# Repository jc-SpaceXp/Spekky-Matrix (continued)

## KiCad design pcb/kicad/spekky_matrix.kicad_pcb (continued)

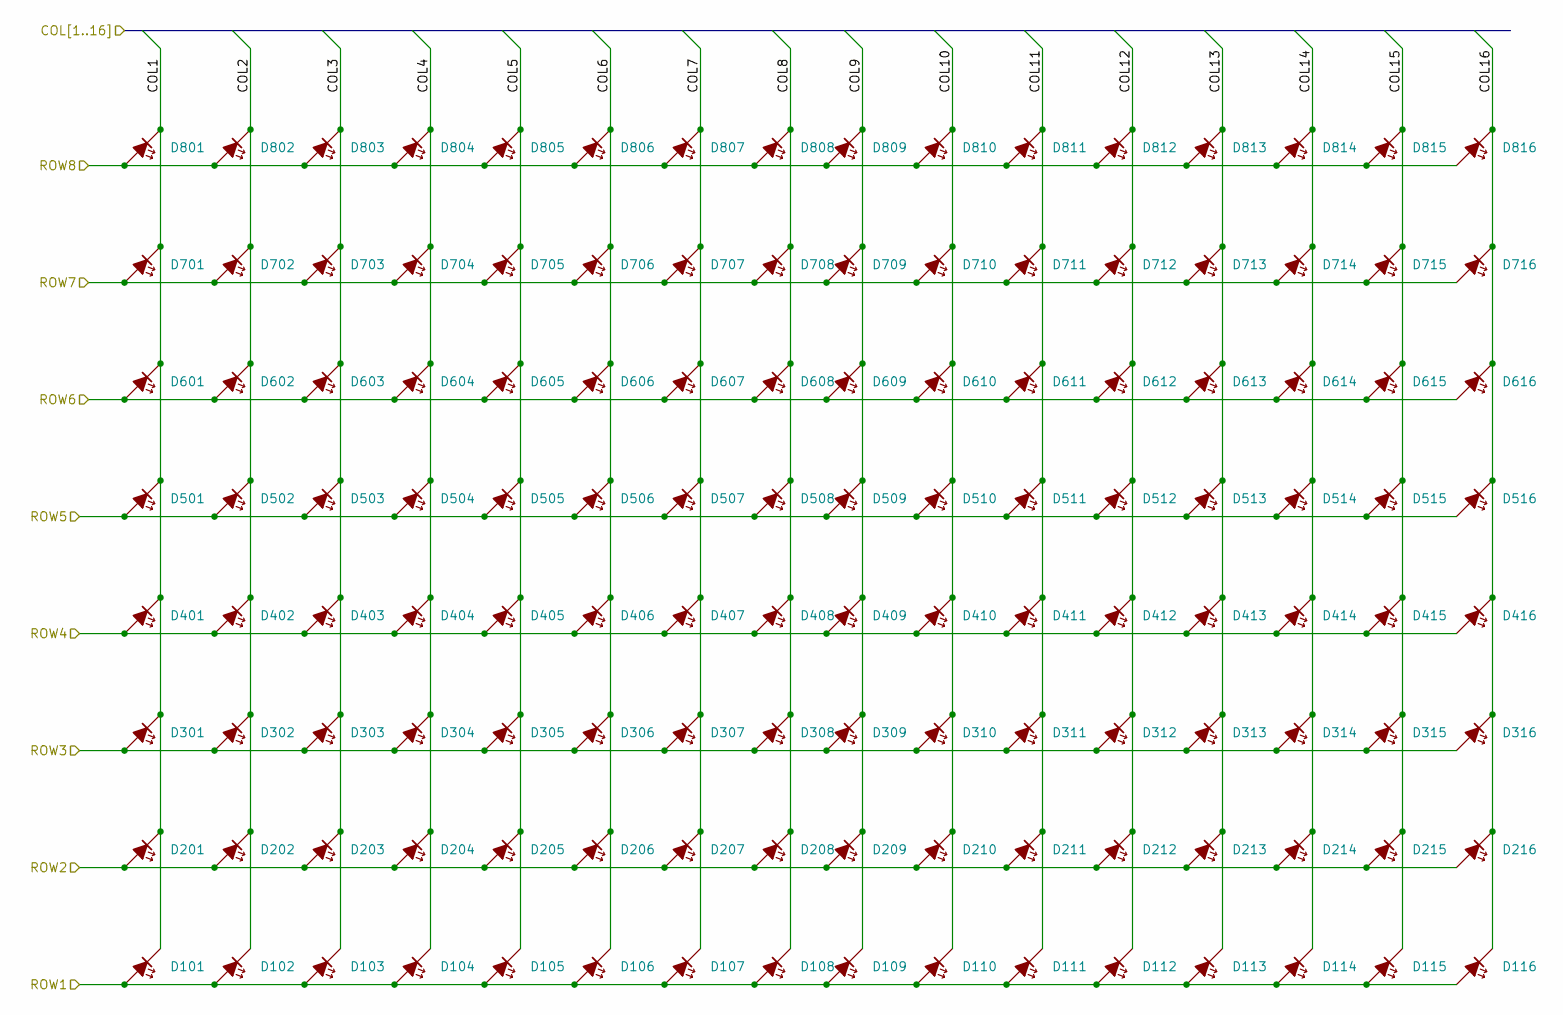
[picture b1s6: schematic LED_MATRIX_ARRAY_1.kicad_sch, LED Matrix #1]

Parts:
D101, D102, D103, D104, D105, D106, D107, D108, D109, D110, D111, D112, D113, D114, D115, D116, D201, D202, D203, D204, D205, D206, D207, D208, D209, D210, D211, D212, D213, D214, D215, D216, D301, D302, D303, D304, D305, D306, D307, D308, D309, D310, D311, D312, D313, D314, D315, D316, D401, D402, D403, D404, D405, D406, D407, D408, D409, D410, D411, D412, D413, D414, D415, D416, D501, D502, D503, D504, D505, D506, D507, D508, D509, D510, D511, D512, D513, D514, D515, D516, D601, D602, D603, D604, D605, D606, D607, D608, D609, D610, D611, D612, D613, D614, D615, D616, D701, D702, D703, D704, D705, D706, D707, D708, D709, D710, D711, D712, D713, D714, D715, D716, D801, D802, D803, D804, D805, D806, D807, D808, D809, D810, D811, D812, D813, D814, D815, D816: LED Matrix (RED); LED_0603_1608Metric_Pad1.05x0.95mm_HandSolder; MPN LTST-C190KRKT

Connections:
/LED DRIVING/COL1: D101.1 (K), D201.1 (K), D301.1 (K), D401.1 (K), D501.1 (K), D601.1 (K), D701.1 (K), D801.1 (K); also elsewhere on the board
/LED DRIVING/COL2: D102.1 (K), D202.1 (K), D302.1 (K), D402.1 (K), D502.1 (K), D602.1 (K), D702.1 (K), D802.1 (K); also elsewhere on the board
/LED DRIVING/COL3: D103.1 (K), D203.1 (K), D303.1 (K), D403.1 (K), D503.1 (K), D603.1 (K), D703.1 (K), D803.1 (K); also elsewhere on the board
/LED DRIVING/COL4: D104.1 (K), D204.1 (K), D304.1 (K), D404.1 (K), D504.1 (K), D604.1 (K), D704.1 (K), D804.1 (K); also elsewhere on the board
/LED DRIVING/COL5: D105.1 (K), D205.1 (K), D305.1 (K), D405.1 (K), D505.1 (K), D605.1 (K), D705.1 (K), D805.1 (K); also elsewhere on the board
/LED DRIVING/COL6: D106.1 (K), D206.1 (K), D306.1 (K), D406.1 (K), D506.1 (K), D606.1 (K), D706.1 (K), D806.1 (K); also elsewhere on the board
/LED DRIVING/COL7: D107.1 (K), D207.1 (K), D307.1 (K), D407.1 (K), D507.1 (K), D607.1 (K), D707.1 (K), D807.1 (K); also elsewhere on the board
/LED DRIVING/COL8: D108.1 (K), D208.1 (K), D308.1 (K), D408.1 (K), D508.1 (K), D608.1 (K), D708.1 (K), D808.1 (K); also elsewhere on the board
/LED DRIVING/COL9: D109.1 (K), D209.1 (K), D309.1 (K), D409.1 (K), D509.1 (K), D609.1 (K), D709.1 (K), D809.1 (K); also elsewhere on the board
/LED DRIVING/COL10: D110.1 (K), D210.1 (K), D310.1 (K), D410.1 (K), D510.1 (K), D610.1 (K), D710.1 (K), D810.1 (K); also elsewhere on the board
/LED DRIVING/COL11: D111.1 (K), D211.1 (K), D311.1 (K), D411.1 (K), D511.1 (K), D611.1 (K), D711.1 (K), D811.1 (K); also elsewhere on the board
/LED DRIVING/COL12: D112.1 (K), D212.1 (K), D312.1 (K), D412.1 (K), D512.1 (K), D612.1 (K), D712.1 (K), D812.1 (K); also elsewhere on the board
/LED DRIVING/COL13: D113.1 (K), D213.1 (K), D313.1 (K), D413.1 (K), D513.1 (K), D613.1 (K), D713.1 (K), D813.1 (K); also elsewhere on the board
/LED DRIVING/COL14: D114.1 (K), D214.1 (K), D314.1 (K), D414.1 (K), D514.1 (K), D614.1 (K), D714.1 (K), D814.1 (K); also elsewhere on the board
/LED DRIVING/COL15: D115.1 (K), D215.1 (K), D315.1 (K), D415.1 (K), D515.1 (K), D615.1 (K), D715.1 (K), D815.1 (K); also elsewhere on the board
/LED DRIVING/COL16: D116.1 (K), D216.1 (K), D316.1 (K), D416.1 (K), D516.1 (K), D616.1 (K), D716.1 (K), D816.1 (K); also elsewhere on the board
/LED DRIVING/ROW1: D101.2 (A), D102.2 (A), D103.2 (A), D104.2 (A), D105.2 (A), D106.2 (A), D107.2 (A), D108.2 (A), D109.2 (A), D110.2 (A), D111.2 (A), D112.2 (A), D113.2 (A), D114.2 (A), D115.2 (A), D116.2 (A); also elsewhere on the board
/LED DRIVING/ROW2: D201.2 (A), D202.2 (A), D203.2 (A), D204.2 (A), D205.2 (A), D206.2 (A), D207.2 (A), D208.2 (A), D209.2 (A), D210.2 (A), D211.2 (A), D212.2 (A), D213.2 (A), D214.2 (A), D215.2 (A), D216.2 (A); also elsewhere on the board
/LED DRIVING/ROW3: D301.2 (A), D302.2 (A), D303.2 (A), D304.2 (A), D305.2 (A), D306.2 (A), D307.2 (A), D308.2 (A), D309.2 (A), D310.2 (A), D311.2 (A), D312.2 (A), D313.2 (A), D314.2 (A), D315.2 (A), D316.2 (A); also elsewhere on the board
/LED DRIVING/ROW4: D401.2 (A), D402.2 (A), D403.2 (A), D404.2 (A), D405.2 (A), D406.2 (A), D407.2 (A), D408.2 (A), D409.2 (A), D410.2 (A), D411.2 (A), D412.2 (A), D413.2 (A), D414.2 (A), D415.2 (A), D416.2 (A); also elsewhere on the board
/LED DRIVING/ROW5: D501.2 (A), D502.2 (A), D503.2 (A), D504.2 (A), D505.2 (A), D506.2 (A), D507.2 (A), D508.2 (A), D509.2 (A), D510.2 (A), D511.2 (A), D512.2 (A), D513.2 (A), D514.2 (A), D515.2 (A), D516.2 (A); also elsewhere on the board
/LED DRIVING/ROW6: D601.2 (A), D602.2 (A), D603.2 (A), D604.2 (A), D605.2 (A), D606.2 (A), D607.2 (A), D608.2 (A), D609.2 (A), D610.2 (A), D611.2 (A), D612.2 (A), D613.2 (A), D614.2 (A), D615.2 (A), D616.2 (A); also elsewhere on the board
/LED DRIVING/ROW7: D701.2 (A), D702.2 (A), D703.2 (A), D704.2 (A), D705.2 (A), D706.2 (A), D707.2 (A), D708.2 (A), D709.2 (A), D710.2 (A), D711.2 (A), D712.2 (A), D713.2 (A), D714.2 (A), D715.2 (A), D716.2 (A); also elsewhere on the board
/LED DRIVING/ROW8: D801.2 (A), D802.2 (A), D803.2 (A), D804.2 (A), D805.2 (A), D806.2 (A), D807.2 (A), D808.2 (A), D809.2 (A), D810.2 (A), D811.2 (A), D812.2 (A), D813.2 (A), D814.2 (A), D815.2 (A), D816.2 (A); also elsewhere on the board

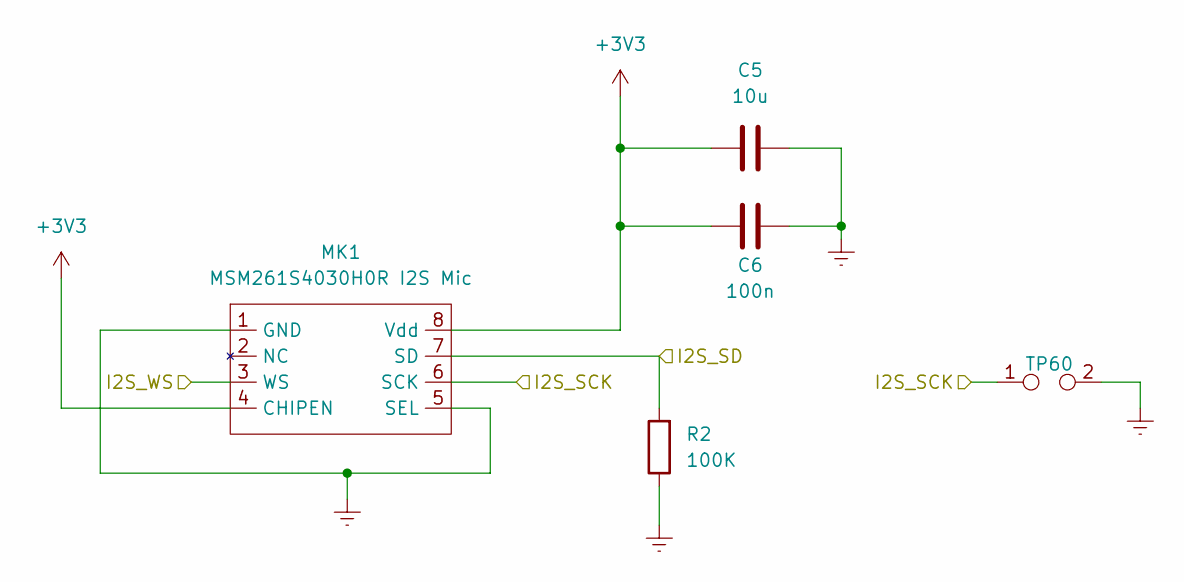
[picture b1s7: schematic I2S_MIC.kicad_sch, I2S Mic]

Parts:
C5: 10u; C_0603_1608Metric; MPN C1608X5R1A106K080AC
C6: 100n; C_0603_1608Metric; MPN C0603C104J3RACTU
MK1: MSM261S4030H0R I2S Mic; LGA-8_2x4_3.0x4.0mm_P1.0mm_Hand_Solder; MPN MSM261S4030H0R
R2: 100K; R_0603_1608Metric; MPN RP73PF1J100KBTDF
TP60: TestPoint_2Pole; D_MicroMELF

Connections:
+3V3: C5.2, C6.2, MK1.4 (CHIPEN), MK1.8 (Vdd); also elsewhere on the board
/I2S MIC/I2S_SCK: MK1.6 (SCK), TP60.1; also elsewhere on the board
/I2S MIC/I2S_SD: MK1.7 (SD), R2.2; also elsewhere on the board
/I2S MIC/I2S_WS: MK1.3 (WS); also elsewhere on the board
GND: C5.1, C6.1, MK1.1 (GND), MK1.5 (SEL), R2.1, TP60.2; also elsewhere on the board

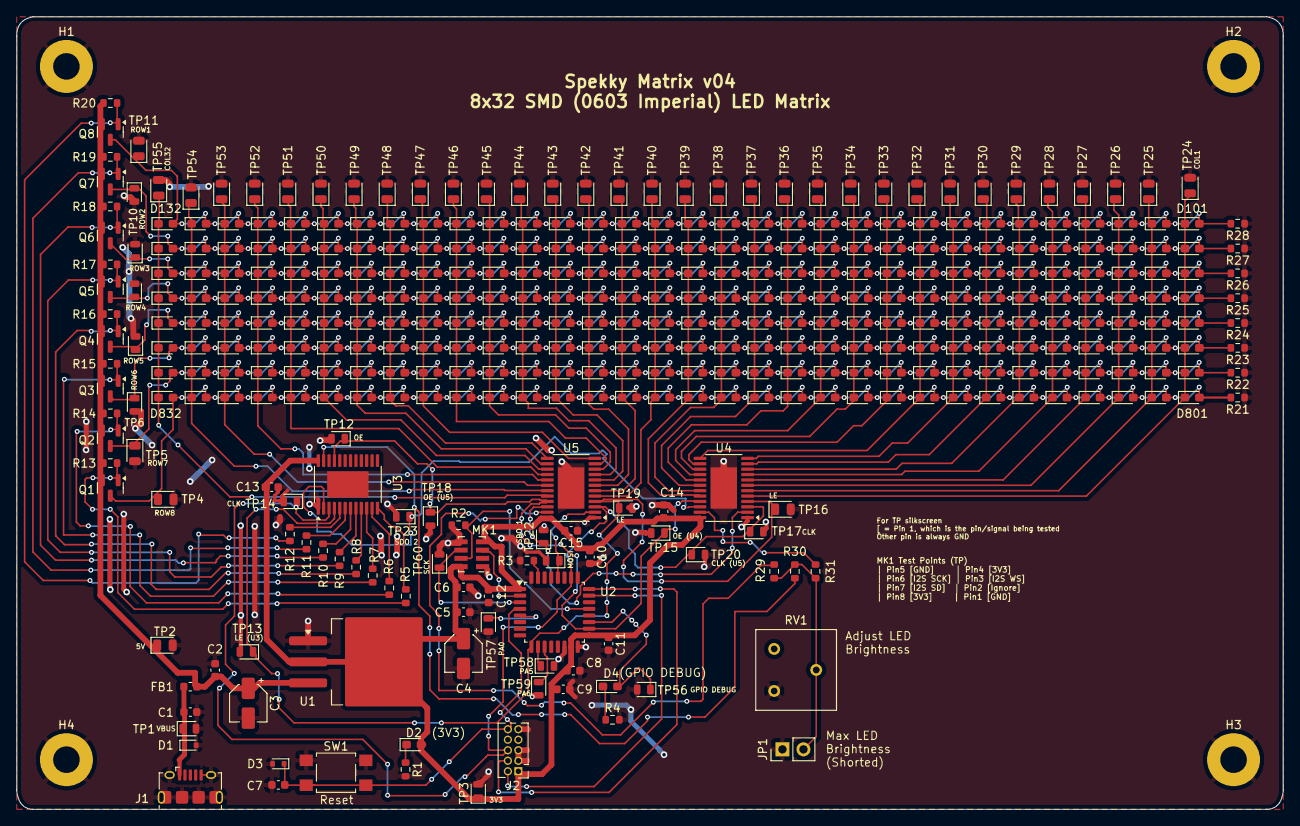
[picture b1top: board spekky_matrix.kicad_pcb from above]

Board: 2 copper layers, 153.0 x 95.8 mm, 390 parts (0 on the bottom side), 83 nets.

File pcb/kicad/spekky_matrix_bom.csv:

"Reference","Qty","MPN","Value","Footprint","DNP"
"C1","1","GCM188R71H103KA37J","10n","Capacitor_SMD:C_0603_1608Metric",""
"C2,C6-C8,C11-C15","9","C0603C104J3RACTU","100n","Capacitor_SMD:C_0603_1608Metric",""
"C3,C4","2","EDH106M016A9BAA","10u","Capacitor_SMD:CP_Elec_4x4.5",""
"C5","1","C1608X5R1A106K080AC","10u","Capacitor_SMD:C_0603_1608Metric",""
"C9","1","GCG188L8EE105KA07D","1u","Capacitor_SMD:C_0603_1608Metric",""
"C10","1","GRM188Z71C475KE21D","4u7","Capacitor_SMD:C_0603_1608Metric",""
"D1,D3","2","PESD5V0X1UAB,115","PESD5V0X1UAB","Diode_SMD:D_SOD-523",""
"D2","1","LTST-C190KRKT","3V3 LED (RED)","LED_SMD:LED_0603_1608Metric_Pad1.05x0.95mm_HandSolder",""
"D4","1","LTST-C190KGKT","GPIO Debug LED (GREEN)","LED_SMD:LED_0603_1608Metric_Pad1.05x0.95mm_HandSolder",""
"D101-D132,D201-D232,D301-D332,D401-D432,D501-D532,D601-D632,D701-D732,D801-D832","256","LTST-C190KRKT","LED Matrix (RED)","LED_SMD:LED_0603_1608Metric_Pad1.05x0.95mm_HandSolder",""
"FB1","1","HI2220R301R-10","300R @ 100 MHz","Inductor_SMD:L_0603_1608Metric",""
"J1","1","10118194-0001LF","USB_B_Micro","Connector_USB:USB_Micro-B_Amphenol_10118194-0001LF_Horizontal",""
"J2","1","FTSH-105-01-L-D-K","Conn_ARM_JTAG_SWD_10","Connector_PinHeader_1.27mm:PinHeader_2x05_P1.27mm_Vertical",""
"MK1","1","MSM261S4030H0R","MSM261S4030H0R I2S Mic","spekky_matrix:LGA-8_2x4_3.0x4.0mm_P1.0mm_Hand_Solder",""
"Q1-Q8","8","DMP3125L-7","DMP3125L-7","Package_TO_SOT_SMD:SOT-23",""
"R1,R4,R13-R20,R29-R31","13","RT0603DRE071KL","1K","Resistor_SMD:R_0603_1608Metric",""
"R2","1","RP73PF1J100KBTDF","100K","Resistor_SMD:R_0603_1608Metric",""
"R3","1","RT0603FRE0710KL","10K","Resistor_SMD:R_0603_1608Metric",""
"R5-R12","8","RT0603FRE0710RL","10R","Resistor_SMD:R_0603_1608Metric",""
"R21-R28","8","RT0603FRE075K1L","5K1","Resistor_SMD:R_0603_1608Metric",""
"RV1","1","3386F-1-222LF","2K2","Potentiometer_THT:Potentiometer_Bourns_3386F_Vertical",""
"SW1","1","TL3305AF260QG","SW_Push","Button_Switch_SMD:SW_SPST_TL3305A",""
"U1","1","LMS1585AIS-3.3/NOPB","LMS1585AIS-3.3","Package_TO_SOT_SMD:TO-263-3_TabPin2",""
"U2","1","STM32G431K8T6","STM32G431K8Tx","Package_QFP:LQFP-32_7x7mm_P0.8mm",""
"U3-U5","3","STP16CP05XTTR ","STP16CP05XT","Package_SO:HTSSOP-24-1EP_4.4x7.8mm_P0.65mm_EP3.2x5mm",""

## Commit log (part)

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2024-05-01 BSP submodule update
    - STM32G431KB update
2024-05-03 Update python fft tests
    - Add option for working with integers rather than floats
2024-05-06 Update CMSIS 6 submodule
2024-05-06 Update main to reflect recent dma changes
    - Dac task is now essentially an idle task as the setup is done before
    all the FreeRTOS code
2024-05-07 Added output of ARM DSP
    - Everything is working as expected, correct bin index and magnitude
    peak (seen on gdb)
    - Dumped gdb array output to text with array indexes to make
    distinguishing real and imaginary values easier
    - Input has to be a complex float, such that x[n] = re(z) and x[n+1] =
    im(z)
2024-05-07 Add python test script file outputs to git ignore
2024-05-08 Update ARM CMSIS 6 submodule
2024-05-08 Remove old c header file from python fft script
    - No longer needed, using ARM DSP, this header was for a different
    submodule
2024-05-09 Make makefile prints easier to see
    - Very hard to see my prints/echos when building this project, added
    some #'s to make those statements more visible (especiall when
    scrolling through the output)
2024-05-20 Place FreeRTOS hooks in its own file
    - Any type of RTOS error handling/hook will be placed in this file in
    the future
    - No header as the FreeRTOS and FreeRTOS tasks headers handle declaring
    the prototype function
    - Unit tests and spekky matrix both compile
2024-05-21 Create oneshot fft timer task
    - I had issues with creating both a oneshot timer "task" and an actual
    preemptive task
    - Kept getting HardFault_Handler errors until I moved the array and
    struct as globals which than gave me a ApplicationStackOverflow error
    (tried this on the oneshot timer)
    - Was able to resolve the oneshot timer method by increasing the timer
2024-06-05 Added STM32 I2S setup for SPI2 module
    - Faced some issues here with my device, looking at the NucleoG431KB
    schematic, PF0 and PF1 (WS and CLK) are both unconnected. Solder
    bridges SB8 and SB11 need to be soldered in order to get an output on
    those pins. Verfied that both WS and CLK were working on my logic
    analyser
    - My I2S MEMS microphone also has a SEL pin which selects which channel
2024-06-07 Remove commented out code
2024-06-18 Add PulseView/Sigrok logic analyser traces
    - With the previous commit I can now graph the logic analyser I2S
    outputs
    - Now have logic analyser traces for:
    1) control (no sound)
    2) 1 kHz sine test tone (played on phone speakers in close proximity
    to Fermion I2S mic)
2024-06-19 Add secondary label for python fft graph
    - Displaying FFT bins as well as frequency too (bins are the top x axis,
    frequency is the bottom, the scalar base on the top left is for the y
    axis e.g. 1e12)
2024-06-19 Refactor fft/ifft graphing code into its own function
2024-06-20 Rename python fft conversion function
    - Function never performed ifft therefore "ifft" bit of string has been
    removed
2024-06-23 Remove TIM2/DAC code from main
    - Timer code is only used for DAC which isn't being used anymore
    - Timer code can also be removed too
2024-06-26 Added new PulseView traces
    - PulseView traces for inverting the I2S idle CLK and a 100K pulldown
    resistor on the I2S SD line
    - Fermion I2S breakout mic also has a 100K pulldown res on SD line too
    as recommended on the I2S mics datasheet
    - Still a couple of non-zero values appear on the R channel but not as
    frequent as before
2024-06-27 Readme: Update submodule list
2024-06-28 Remove awkward 10^x on y axis python FFT graph
    - 10^x label overlaps with the FFT bins top x axis
    - Now 10^x is on each tick on the y axis in scientific notation e.g.
    1.20e11
2024-06-28 Fix readme spacing
2024-09-07 Squashed commit of the following:
    - Opted for squash commit to keep main branch buildable, there was many
    intermediatte commits and hotfixes which shouldn't be on the main
    branch as is
    - Summary of commits:
    1) Processing all incoming I2S mic data into a one channel buffer (w/
    unit tests) (I2S DMA conversion)
2024-09-11 Add kicad pdf schematic of project
    - This is my current schematic which I've implemented by using the
    manhattan prototyping method
    - I consider v01 the single non-cascaded LED matrix version
    - v02 is the 4 cascaded LED matrices
    - Only the pdf for now, I may consider uploading the kicad project later
    as well
2024-09-13 Asan support makefile
2024-09-26 Get timings for led matrix (real speed)
    - Converted LED matrix callback into a task
    - Therefore the only tasks are the IDLE and LED matrix
    - Removed I2S/DMA code as it isn't needed for this timing test
    - Undo the SPI_CLK/8 change to see if we can get an accurate timing of
    the LED matrix task (know it should be ~60us/8 per row, ~60us total)
2024-09-26 Add PulseView traces for spi transfer time
    - Around about 80-90us for the SPI updates to all 4 matrices
2024-09-26 Setup for dma/i2s and fft code only
    - Next commits will be for dma timings and fft task timings
2024-09-26 Get timing for dma to complex data conversion
2024-09-26 Add PulseView traces for fft bin magnitudes
    - As predicted the measured time for FFT bin magnitude calculations was
    150-158us (lo-hi transition time)
    - Can now create an execution timeline figure to add to the project
2024-10-01 New fft led bar sensitivities
    - Skipping the associated unit test until we come up with the final
    values
    - Previous values are way too sensitive, all frequencies have about 4-5
    bars in ambient environments
2024-10-03 Python fft for integer test use square wave
    - Was previously using a sine wave for the configuration of the fft
    - However, seeing as the I2S data is already a 1 kHz wave we are better
    off using a square at max amplitude
    - A square wave at max amplitude allows me to dial in my dB scaling to
    see if it is correct or not
2024-10-04 Capture fft bin magnitude data for max amp square wave
    - Format is 24-bit LSB padding hence 0xFFFFFF00 which is -256 as an int
    positive half cycle
    - Must keep the DMA code as well otherwise a hardfault occurs
2024-10-04 Capture fft bin mags of 24-bit square wave
    - Same test as before except data is LSB padded to 32-bits
2024-10-04 Correct array size in extern declaration
2024-10-05 Add averaging function for 2d arrays
    - Function needed for getting an average that will be fed into the db FS
    conversion function e.g. 6 FFTs into one dB FS calculation
2024-10-05 Additional unit test for averaging function
2024-10-05 Implement fft averaging double buffering via constants
    - Can now just update the fft_constants header file rather than relying
    on hard coded values for FFT averaging double buffering
2024-10-07 Update python fft default options
2024-10-07 Add fixed frequency sine wave output videos
    - 2kHz and 4kHz sine from a youtube video played on my speakers
    - Video are H265 encoded for size
    - Gifs are always large, scaled down to 640x360 to keep the size
    somewhat respectable
2024-10-08 Added sine sweep gif
    - Again used Ffmpeg for this, needed to follow their wiki for "how to
    speed up / slow down a vide", converted to raw h265 and sped up by 2.5
    times speed into a new mp4 file which was then used for a gif
    conversion with the new FPS and gif FPS both matching
    - Found out that changing the FPS of the gif didn't really speed up or
    slow down the video how I wanted
2024-10-31 Update schematic
    - Added no connect pins to unused pins
2024-11-21 Update schematic
    - STM32 part of schematic has been updated, intended to work without the
    Nucelo board now
    - Mostly taken from Nucleo design (VDDA/VDD and GNDA/GND shorts will
    most likely be replaced)
2024-11-26 Update schematic
    - Using USB B micro connector over the bulky USB A
    - Grounded USB shield
    - 5V is now LDO input rather than VBUS to avoid a stubbed VBUS
    transmission line on the PCB
2025-01-25 Led matrix bar function partially supports 16x16 led matricies
    - Required for different LED matrix IC drivers, some expect 16-bit SPI
    transfers, others 8 bit
    - Currently only supporting 8 bits
    - Now supporting 16-bits for RightToLeft and LeftToRight led enum
    directions which supports 16-pixel width (currently hard coded for 8
    rows but could be expanded to 16 rows without any issues)
2025-04-14 Make led cascade function a max7219 specific one
    - Renamed and changed args to be more in line with other recent changes
2025-04-24 Add a generic function for cascaded led driver ics
    - New enum for reversal of cascaded data order e.g. if data is in an
    array as device1 then device 2, reversal will output device2 then
    device1 over SPI (otherwise it is output in the order it's stored in)
    - Added unit test
2025-05-06 Update schematic
    - Updated TVS diodes part names, previously was using a placeholder
    - Believe the TVS diode should be fine for the push button, ideally
    would want a lower reverse standoff voltage but the NRST pin is 5V
    tolerable (therefore shouldn't be an issue)
2025-05-14 Update parts/mpns/descriptions etc.
    - Incorrect LED part, was 0805 package instead of 0603
    - Added MPNs for other parts (mostly ones I already own multiples of)
    - Update schematics?
2025-05-22 Add comment for pb3 (spi_clk/swo)
    - PB3 is being used for SPI_CLK
    - However is also connected to SWO, the programmer can choose to enable
    SWO at the cost of losing SPI_CLK (maybe useful for debug stages)
2025-06-06 Add pcb constraint settings (oshpark)
    - Used OSHPark constraints and haven't had any issues with either
    Elecrow or OSHPark
2025-06-13 Move d3 on pcb (line up nrst signals vertically)
2025-06-14 Add custom symbols (lga) to project
    - Not included in project until now
    - No ERC error/warnings now
2025-06-25 Connect spi traces
2025-06-25 Connect potentiometer traces
2025-06-26 Correct nrst switch connections
    - Moved ESD diode and capacitor to remove any stubbing on the
    transmission line
2025-06-26 Update pcb footprint on mosfets
2025-06-26 Update pcb footprint for jumper pins (jp1)
2025-06-26 Thicker gnd trace for via
2025-06-26 Route all ground zones and pins
    - Connected isolated ground zones and pins
    - No connections unrouted
2025-06-26 Update lga hand solder footprint
    - Pin1 silkscreen was causing issues, would be masked by front copper
    for pin 1
2025-06-27 Update shcematic
    - Schematic with new test points from previous commits
2025-06-27 Increase pcb titles size
2025-06-29 Minor changes to tracks/vias for better signal integrity
    - Moving tracks/vias to create larger ground fill zones for better
    signal integrity
    - Also adding more clearance between certain tracks
2025-06-30 Add bom csv file
2025-06-30 Add 3d renders to readme and repo
2025-08-01 Correct 10k resistor part number
2025-09-23 Update pcb png renders
2025-11-01 Correct stm32 outputs for led driver ic
    - SPI CS is analogous to LE, but was instead mapped to OE which in my
    initial tests were tied to GND (all LEDs could be driven)
    - Now SPI CS has been renamed to OE and is still mapped to OE pin on the
    STP led driver IC
    - GPIO LE is now correctly mapped the LE input on the STP too
2025-11-01 Pull oe to gnd
    - OE needs to be pulled to GND if we wish to set any LED (drives the
    outputs of each STP16 led driver IC)
2025-11-03 Minor changes to gpio debug setup
    - Correct a misleading comment (copy-paste error)
    - Deleted whitespace between inversion operator and operand (formatting)
2025-11-03 Use spi port macros over gpio macros for struct init
    - Easier to maintain, just need to change the header file if any issues
    with ports or pin
2025-12-06 Add 32-bit function for setting rows in led matrix
    - Using 32-bits to represent each column of data per row
    - Added new unit tests for some 32-bit checks
    - Some unit tests are broken now after changing how the shifting
    conversion works
2025-12-17 Remove led direction enum from matrix function
    - Matrix conversion function is purely focused on conversion of led
    height/length data to the matrix
    - Another function will take this matrix data and perform the inversions
    instead
2025-12-17 Refactor led matrix 32 bit inversion unit tests
    - Uses a looped unit test with the data all in one function rather than
    copying and pasting the same unit test over and over again
2025-12-17 Formatting of pointer data type in function
2025-12-17 Rename 32 bit led matrix bar conversion function
2026-01-04 Replace test point footprints
    - Quite difficult to probe the 0402 SMD sized test points with my PCBite
    probes
    - End up scraping up the PCB trying to probe my test points as the gap
    is too small (on the 0402 footprint)
    - The 0805 and microMELF footprints are appropriately sized for hands
    free probing
